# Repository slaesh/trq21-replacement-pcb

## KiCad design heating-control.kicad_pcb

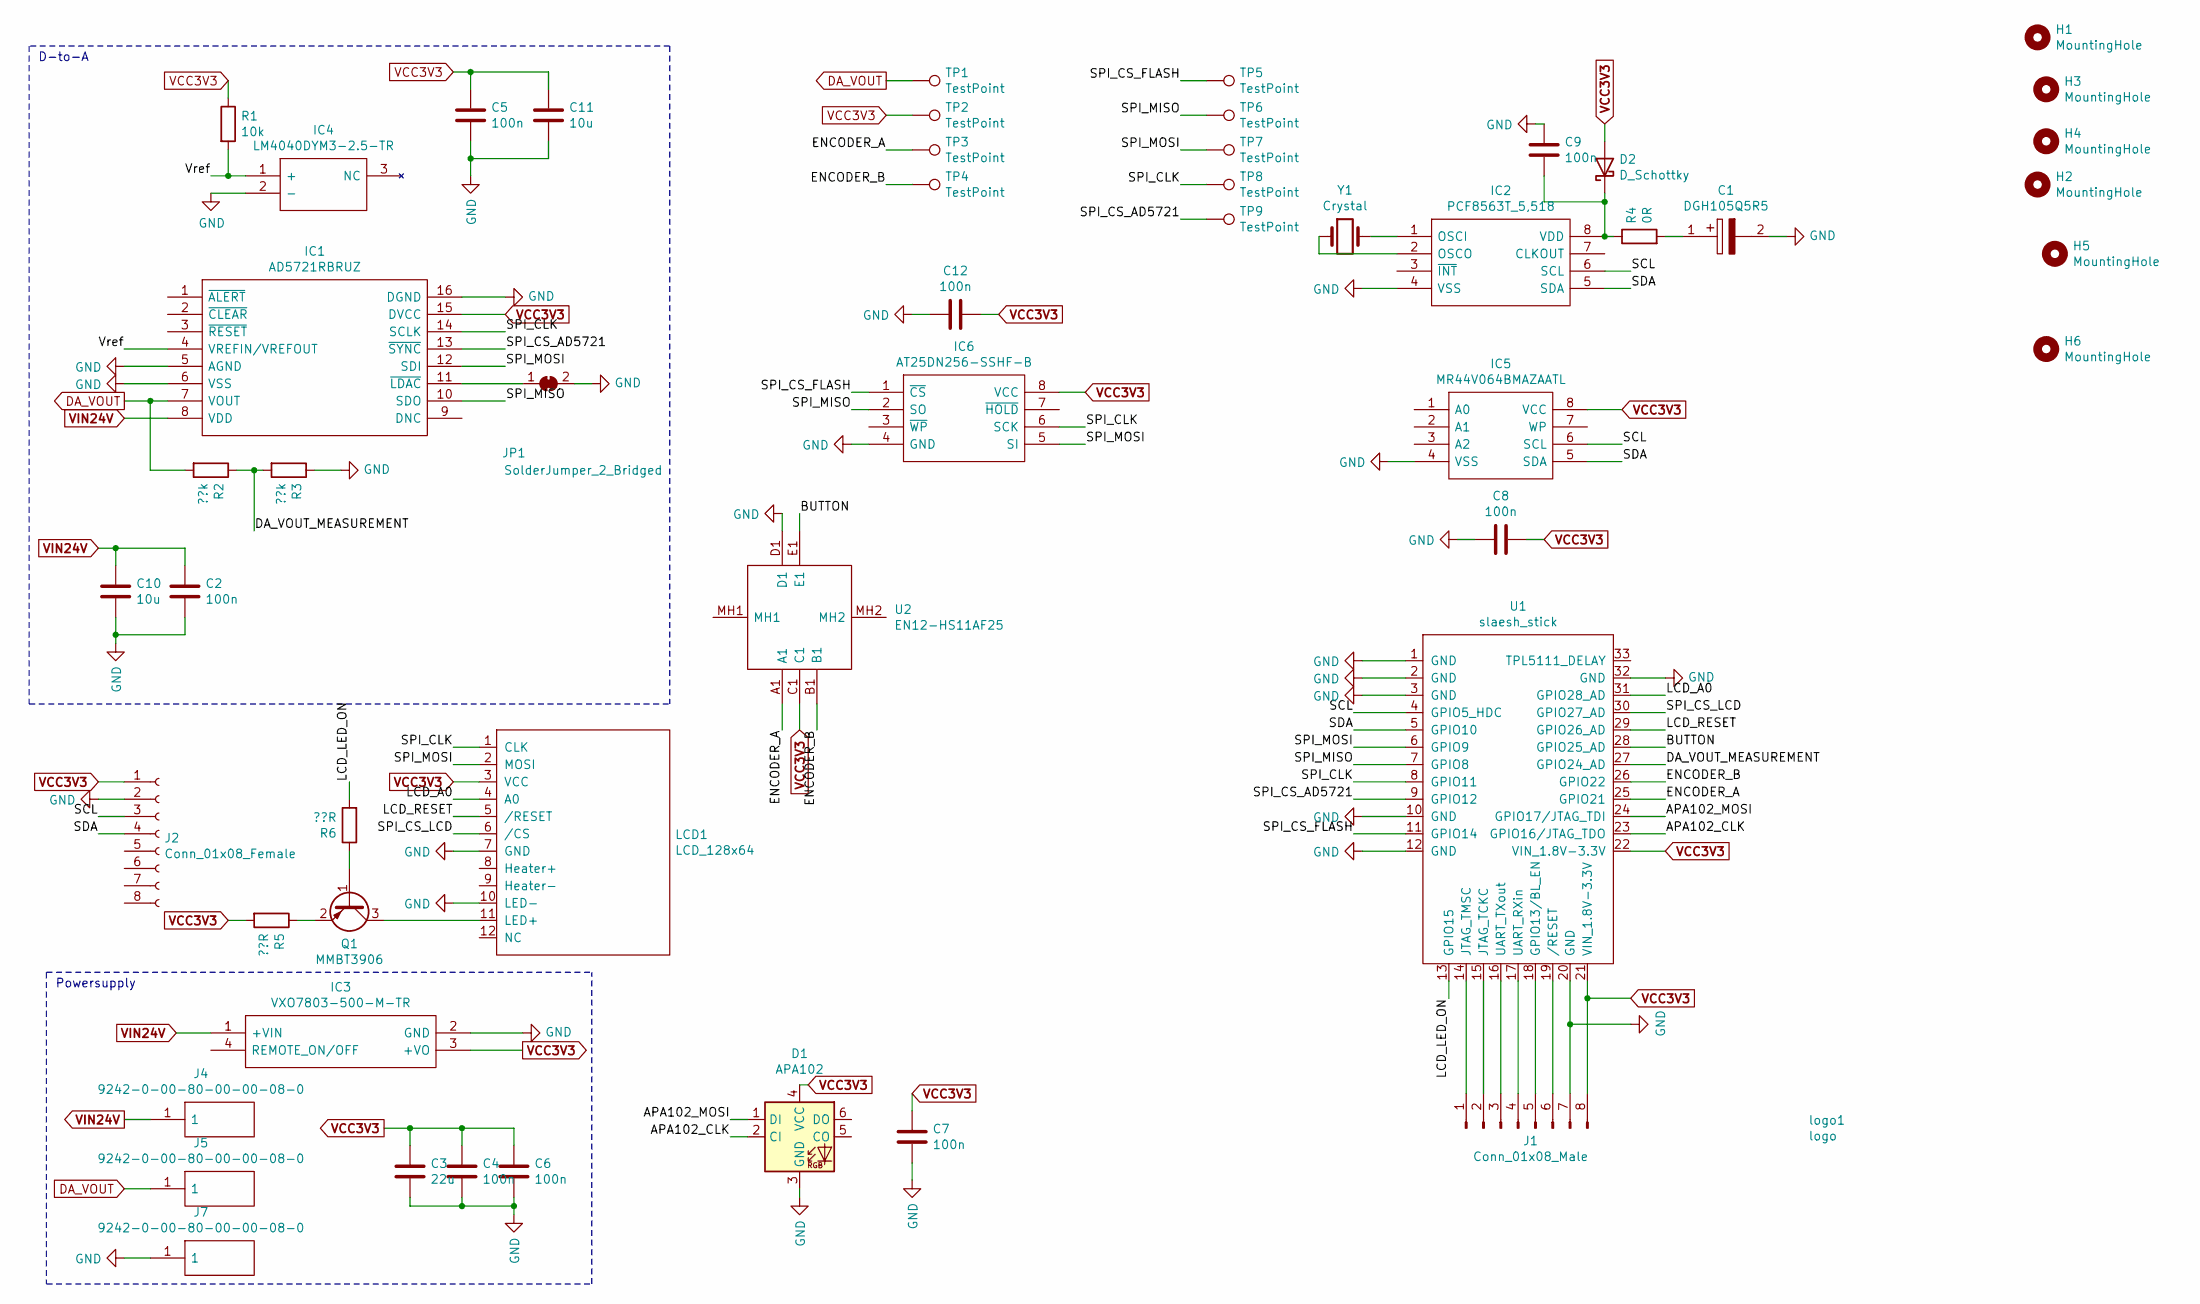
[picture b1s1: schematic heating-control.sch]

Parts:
C1: DGH105Q5R5; Manufacturer_Part_Number DGH105Q5R5
C2, C4, C5, C6, C7, C8, C9, C12: 100n; C_0603_1608Metric
C3: 22u; C_0603_1608Metric
C10, C11: 10u; C_0603_1608Metric
D1: APA102; LED_RGB_5050-6
D2: D_Schottky; D_SOD-323
H1, H2, H3, H4, H5, H6: MountingHole; MountingHole_3.2mm_M3_Pad_Via
IC1: AD5721RBRUZ; SOP65P640X120-16N; Mouser2 Part Number 584-AD5721RBRUZ
IC2: PCF8563T_5,518; SOIC127P600X175-8N; Manufacturer_Part_Number PCF8563T/5,518
IC3: VXO7803-500-M-TR; VXO7803500MTR; Manufacturer_Part_Number VXO7803-500-M-TR
IC4: LM4040DYM3-2.5-TR; SOT95P237X111-3N; Manufacturer_Part_Number LM4040DYM3-2.5-TR
IC5: MR44V064BMAZAATL; SOIC127P600X165-8N; Mouser2 Part Number 755-MR44V064BMAZAATL
IC6: AT25DN256-SSHF-B; SOIC127P600X175-8N; Manufacturer_Part_Number AT25DN256-SSHF-B
J1: Conn_01x08_Male; PinHeader_1x08_P2.54mm_Vertical
J2: Conn_01x08_Female; PinHeader_1x08_P2.54mm_Vertical
J4, J5, J7: 9242-0-00-80-00-00-08-0; 9242000800000080; Manufacturer_Part_Number 9242-0-00-80-00-00-08-0
JP1: SolderJumper_2_Bridged; SolderJumper-2_P1.3mm_Bridged2Bar_RoundedPad1.0x1.5mm
LCD1: LCD_128x64; lcd_test
Q1: MMBT3906; SOT-23
R1: 10k; R_0603_1608Metric
R2, R3: ??k; R_0603_1608Metric
R4: 0R; R_0603_1608Metric
R5, R6: ??R; R_0603_1608Metric
TP1, TP2, TP3, TP4, TP5, TP6, TP7, TP8, TP9: TestPoint; TestPoint_Keystone_5000-5004_Miniature
U1: slaesh_stick
U2: EN12-HS11AF25; EN12HS11AF25; Manufacturer_Part_Number EN12-HS11AF25
Y1: Crystal; SMD3215_2P32768KHZ125PF10PPM
logo1: logo; logo_me

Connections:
/APA102_CLK: D1.2 (CI), U1.23 (GPIO16/JTAG_TDO)
/APA102_MOSI: D1.1 (DI), U1.24 (GPIO17/JTAG_TDI)
/BUTTON: U1.28 (GPIO25_AD), U2.E1
/DA_VOUT_MEASUREMENT: R2.1, R3.2, U1.27 (GPIO24_AD)
/ENCODER_A: TP3.1, U1.25 (GPIO21), U2.A1
/ENCODER_B: TP4.1, U1.26 (GPIO22), U2.B1
/LCD_A0: LCD1.4 (A0), U1.31 (GPIO28_AD)
/LCD_LED_ON: R6.2, U1.13 (GPIO15)
/LCD_RESET: LCD1.5 (/RESET), U1.29 (GPIO26_AD)
/SCL: IC2.6 (SCL), IC5.6 (SCL), J2.3, U1.4 (GPIO5_HDC)
/SDA: IC2.5 (SDA), IC5.5 (SDA), J2.4, U1.5 (GPIO10)
/SPI_CLK: IC1.14 (SCLK), IC6.6 (SCK), LCD1.1 (CLK), TP8.1, U1.8 (GPIO11)
/SPI_CS_AD5721: IC1.13 (~SYNC), TP9.1, U1.9 (GPIO12)
/SPI_CS_FLASH: IC6.1 (~CS), TP5.1, U1.11 (GPIO14)
/SPI_CS_LCD: LCD1.6 (/CS), U1.30 (GPIO27_AD)
/SPI_MISO: IC1.10 (SDO), IC6.2 (SO), TP6.1, U1.7 (GPIO8)
/SPI_MOSI: IC1.12 (SDI), IC6.5 (SI), LCD1.2 (MOSI), TP7.1, U1.6 (GPIO9)
/Vref: IC1.4 (VREFIN/VREFOUT), IC4.1 (+), R1.2
DA_VOUT: IC1.7 (VOUT), J5.1, R2.2, TP1.1
GND: C1.2, C2.2, C3.2, C4.2, C5.2, C6.2, C7.2, C8.1, C9.1, C10.2, C11.2, C12.1, D1.3 (GND), IC1.5 (AGND), IC1.6 (VSS), IC1.16 (DGND), IC2.4 (VSS), IC3.2 (GND), IC4.2 (-), IC5.4 (VSS), IC6.4 (GND), J1.7, J2.2, J7.1, JP1.2 (B), LCD1.7 (GND), LCD1.10 (LED-), R3.1, U1.1 (GND), U1.2 (GND), U1.3 (GND), U1.10 (GND), U1.12 (GND), U1.20 (GND), U1.32 (GND), U2.D1
unnamed: C1.1, R4.2
unnamed: C9.2, D2.1 (K), IC2.8 (VDD), R4.1
unnamed: IC1.11 (~LDAC), JP1.1 (A)
unnamed: IC2.1 (OSCI), Y1.2
unnamed: IC2.2 (OSCO), Y1.1
unnamed: J1.1, U1.14 (JTAG_TMSC)
unnamed: J1.2, U1.15 (JTAG_TCKC)
unnamed: J1.3, U1.16 (UART_TXout)
unnamed: J1.4, U1.17 (UART_RXin)
unnamed: J1.5, U1.18 (GPIO13/BL_EN)
unnamed: J1.6, U1.19 (/RESET)
unnamed: LCD1.11 (LED+), Q1.3 (C)
unnamed: Q1.1 (B), R6.1
unnamed: Q1.2 (E), R5.1
VCC3V3: C3.1, C4.1, C5.1, C6.1, C7.1, C8.2, C11.1, C12.2, D1.4 (VCC), D2.2 (A), IC1.15 (DVCC), IC3.3 (+VO), IC5.8 (VCC), IC6.8 (VCC), J1.8, J2.1, LCD1.3 (VCC), R1.1, R5.2, TP2.1, U1.21 (VIN_1.8V-3.3V), U1.22 (VIN_1.8V-3.3V), U2.C1
VIN24V: C2.1, C10.1, IC1.8 (VDD), IC3.1 (+VIN), J4.1

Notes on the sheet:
Powersupply
D-to-A

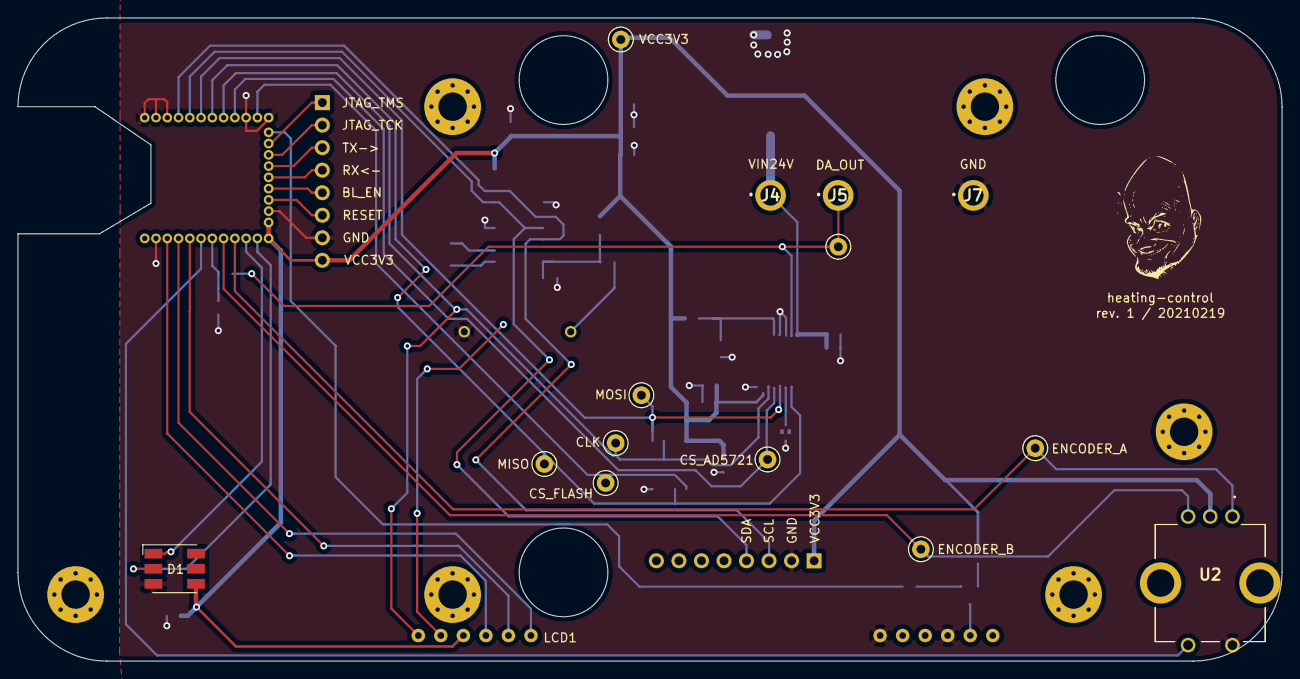
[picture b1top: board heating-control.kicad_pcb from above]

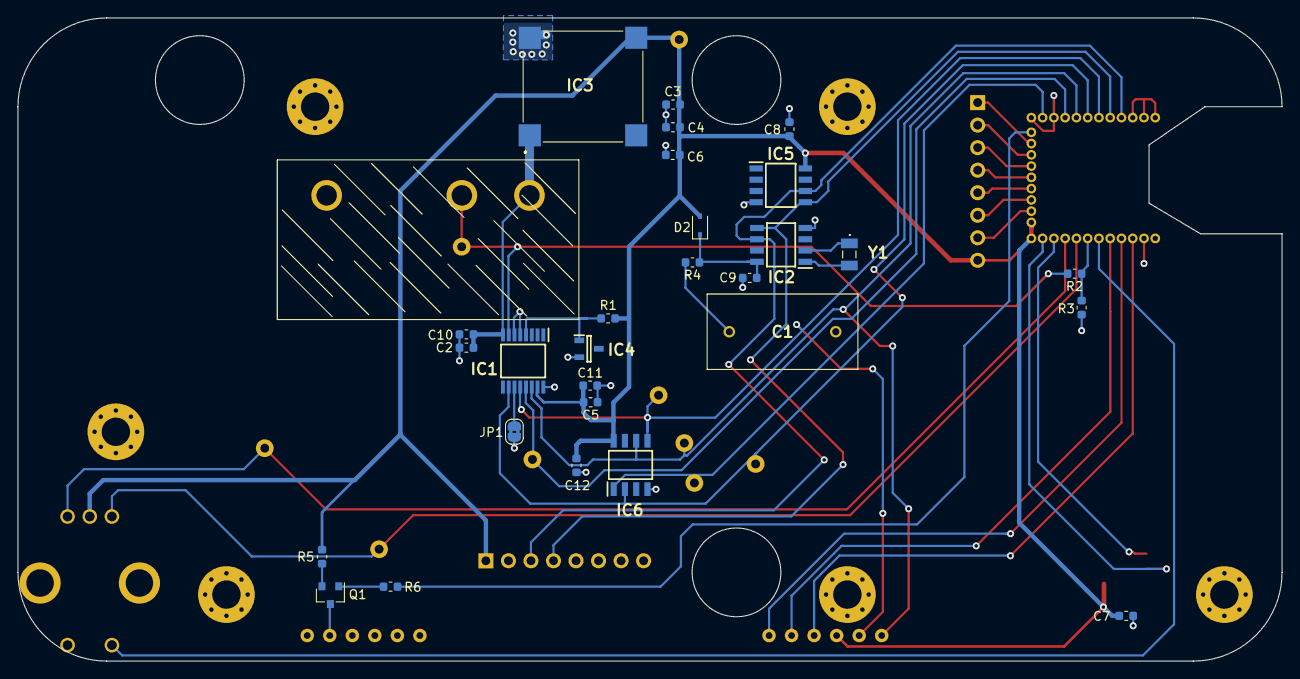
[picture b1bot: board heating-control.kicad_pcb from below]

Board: 2 copper layers, 142.5 x 72.5 mm, 53 parts (29 on the bottom side), 36 nets.

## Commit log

2021-02-18 add git ignore
2021-02-19 rev1
2021-02-19 rev1 annotations
2021-11-29 latest version
